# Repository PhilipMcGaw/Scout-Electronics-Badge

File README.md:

====== Electronics badge ======

How to earn your badge:

  - Identify a number of common electronic components that are shown to you.
    - Explain, in simple terms, the functions they perform in electronic circuits.
  - Describe the systems used for marking components with their values
    - Demonstrate by identifying the values of resistors and capacitors by their markings. Explain the importance of the rating of a component.
  - Show that you know the symbols used to represent common components in circuit diagrams.
    - Show how to identify the polarity of a diode and a specific PIN on an integrated circuit.
  - Show that you’re aware of the safe working practices to be followed when handling electronic components, circuit boards and when soldering.
  - Use a multimeter to measure voltage, current and resistance in a simple circuit.
    - Explain the relationship between these values.
  - Talk about the main differences in the operation of digital and analogue circuits.
  - Construct three simple circuits.
    - One of these should be based mainly on digital electronics. They can be from a book or magazine, or you can design the circuits yourself. If possible, at least one of the circuits should be soldered using either stripboard or a custom-made printed circuit board.
  - Explain the principles behind the operation of each circuit and the typical values of voltage and current found in each.
  - Explain the possible uses of the three circuits you built.
  - Talk about the uses and benefits of electronics in everyday life.
    - Explain how electronics can be used to improve lives.

| Number  | Title                                                                                                                     | 1  | 2  | 3  | 4  | 5  | 6  | 7  | 8  | 9  | 10  |
| 1.      | Learn about resistors https://www.scouts.org.uk/activities/learn-about-resistors/                                         |    | 2  |    |    |    |    |    |    |    |     |
| 2.      | Ready https://www.scouts.org.uk/activities/ready-steady-solder/                                                           |    |    |    | 4  |    |    |    |    |    |     |
| 3.      | Multimeter multi-you https://www.scouts.org.uk/activities/multimeter-multi-you/                                           |    |    |    |    | 5  |    |    |    |    |     |
| 4.      | Thinking logically https://www.scouts.org.uk/activities/thinking-logically/                                               |    |    |    |    |    | 6  |    |    |    |     |
| 5.      | Brush bugs https://www.scouts.org.uk/activities/brush-bugs/ / https://kitronik.co.uk/blogs/resources/iet-scout-brush-bug  |    |    |    |    |    |    | 7  | 8  | 9  |     |
| 6.      | Fruit and Vegetable Power Challenge https://www.scouts.org.uk/activities/fruit-and-vegetable-power-challenge/             |    |    |    |    |    |    | 7  |    |    |     |
| 7.      | LEDs Celebrate https://www.scouts.org.uk/activities/leds-celebrate/                                                       |    |    |    |    |    |    | 7  | 8  | 9  |     |
| 8.      | Make an electric car https://www.scouts.org.uk/activities/make-an-electric-car/                                           |    |    |    |    |    |    | 7  |    |    |     |
| 9.      | Making rainbows https://www.scouts.org.uk/activities/making-rainbows/                                                     |    |    |    |    |    |    | 7  | 8  | 9  |     |
| 10.     | Power a lightbulb using potato energy https://www.scouts.org.uk/activities/power-a-lightbulb-using-potato-energy/         |    |    |    |    |    |    |    |    |    | 10  |

  * https://kitronik.co.uk/blogs/resources/scout-electronics-badge-resources
  * https://www.scouting.org/merit-badges/electronics/
  * https://cobargoscouts.org.au/jota-joti-electronics.html

  - Describe the safety precautions you must exercise when using, building, altering, or repairing electronic devices.
  - Do the following:
    - Draw a simple schematic diagram. It must show resistors, capacitors, and transistors or integrated circuits. Use the correct symbols. Label all parts.
    - Tell the purpose of each part.
  - Do the following:
    - Show the right way to solder and desolder.
    - Show how to avoid heat damage to electronic components.
    - Tell about the function of a printed circuit board. Tell what precautions should be observed when soldering printed circuit boards.
  - Do the following:
    - Discuss each of the following with your counselor:
      - How to use electronics for a control purpose.
      - Explain the basic principles of digital logic.
      - How to use electronics for three different analog applications.
    - Show how to change three decimal numbers into binary numbers and three binary numbers into decimal numbers.
    - Choose ONE of the following THREE projects. For your project, find or create a schematic diagram. To the best of your ability, explain to your counselor how the circuit you built operates.
      - A control device
      - A digital circuit
      - An analog circuit.
  - Do the following:
    - Show how to solve a simple problem involving current, voltage, and resistance using Ohm's law
    - Tell about the need for and the use of test equipment in electronics. Name three types of test equipment. Tell how they operate.
    - Demonstrate to your counsellor how to read the colored bands of a resistor to determine its resistance value.
    - Explain the differences between Through Hole and Surface Mount assembly technologies and give three advantages of each.
  - Identify three career opportunities that would use skills and knowledge in Electronics. Pick one and research the training, education, certification requirements, experience, and expenses associated with entering the field. Research the prospects for employment, starting salary, advancement opportunities and career goals associated with this career. Discuss what you learned with your counselor and whether you might be interested in this career.

  https://docs.franzininho.com.br/docs/franzininho-diy/sobre#projeto-open-hardware

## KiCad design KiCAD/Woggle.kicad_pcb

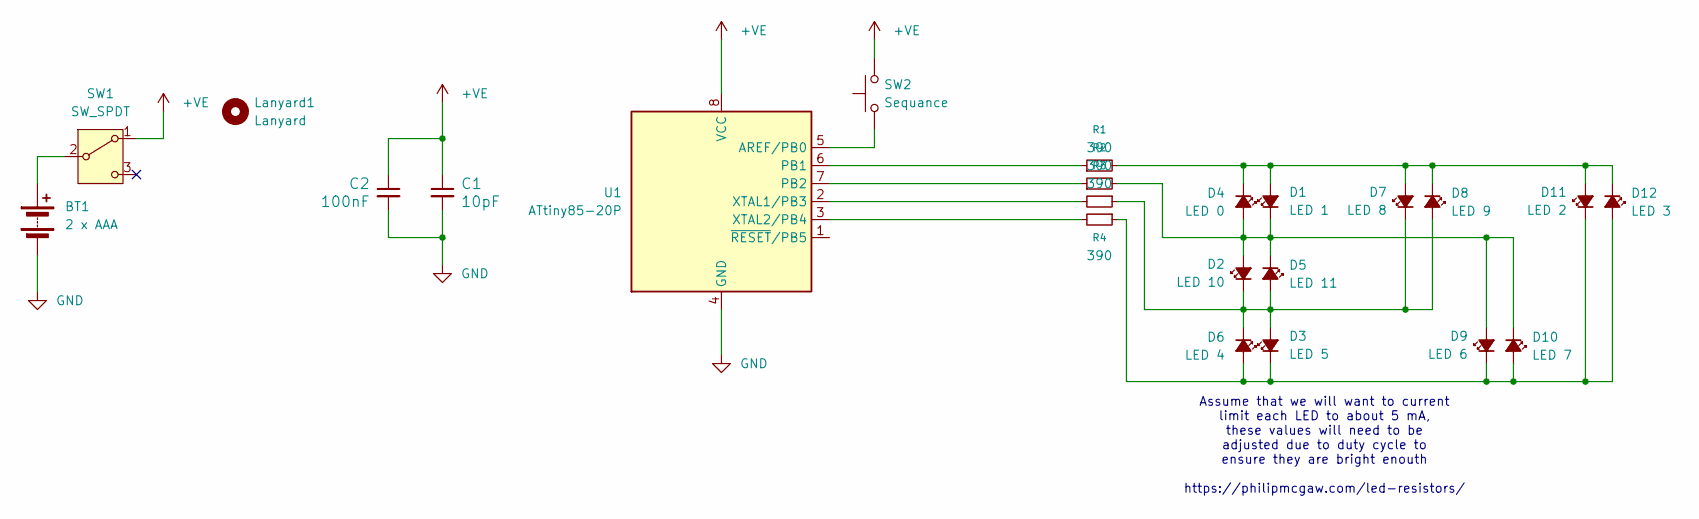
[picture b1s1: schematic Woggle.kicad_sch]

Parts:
BT1: 2 x AAA; Scouts - 2 x AAA battery cell holder
C1: 10pF; C_Disc_D4.7mm_W2.5mm_P5.00mm
C2: 100nF; C_Disc_D4.7mm_W2.5mm_P5.00mm
D1: LED 1; Scouts - 5mm LED
D2: LED 10; Scouts - 5mm LED
D3: LED 5; Scouts - 5mm LED
D4: LED 0; Scouts - 5mm LED
D5: LED 11; Scouts - 5mm LED
D6: LED 4; Scouts - 5mm LED
D7: LED 8; Scouts - 5mm LED
D8: LED 9; Scouts - 5mm LED
D9: LED 6; Scouts - 5mm LED
D10: LED 7; Scouts - 5mm LED
D11: LED 2; Scouts - 5mm LED
D12: LED 3; Scouts - 5mm LED
Lanyard1: Lanyard; MountingHole_5mm
R1, R2, R3, R4: 390; Scouts - Resistor (10.16mm)
SW1: SW_SPDT; SW_Slide_SPDT_Angled_CK_OS102011MA1Q
SW2: Sequance; SW_PUSH-12mm
U1: ATtiny85-20P; Scouts - DIP 8

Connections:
+VE: C1.1, C2.1, SW1.1 (A), SW2.2, U1.8 (VCC)
GND: BT1.2 (-), C1.2, C2.2, U1.4 (GND)
unnamed: BT1.1 (+), SW1.2 (B)
unnamed: D1.2 (A), D4.1 (K), D7.2 (A), D8.1 (K), D11.2 (A), D12.1 (K), R1.2
unnamed: D1.1 (K), D2.2 (A), D4.2 (A), D5.1 (K), D9.2 (A), D10.1 (K), R2.2
unnamed: D2.1 (K), D3.2 (A), D5.2 (A), D6.1 (K), D7.1 (K), D8.2 (A), R3.1
unnamed: D3.1 (K), D6.2 (A), D9.1 (K), D10.2 (A), D11.1 (K), D12.2 (A), R4.1
unnamed: SW2.1, U1.5 (AREF/PB0)
unnamed: R1.1, U1.6 (PB1)
unnamed: R2.1, U1.7 (PB2)
unnamed: R3.2, U1.2 (XTAL1/PB3)
unnamed: R4.2, U1.3 (XTAL2/PB4)

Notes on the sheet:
Assume that we will want to current limit each LED to about 5 mA, these values will need to be adjusted due to duty cycle to ensure they are bright enouth https://philipmcgaw.com/led-resistors/

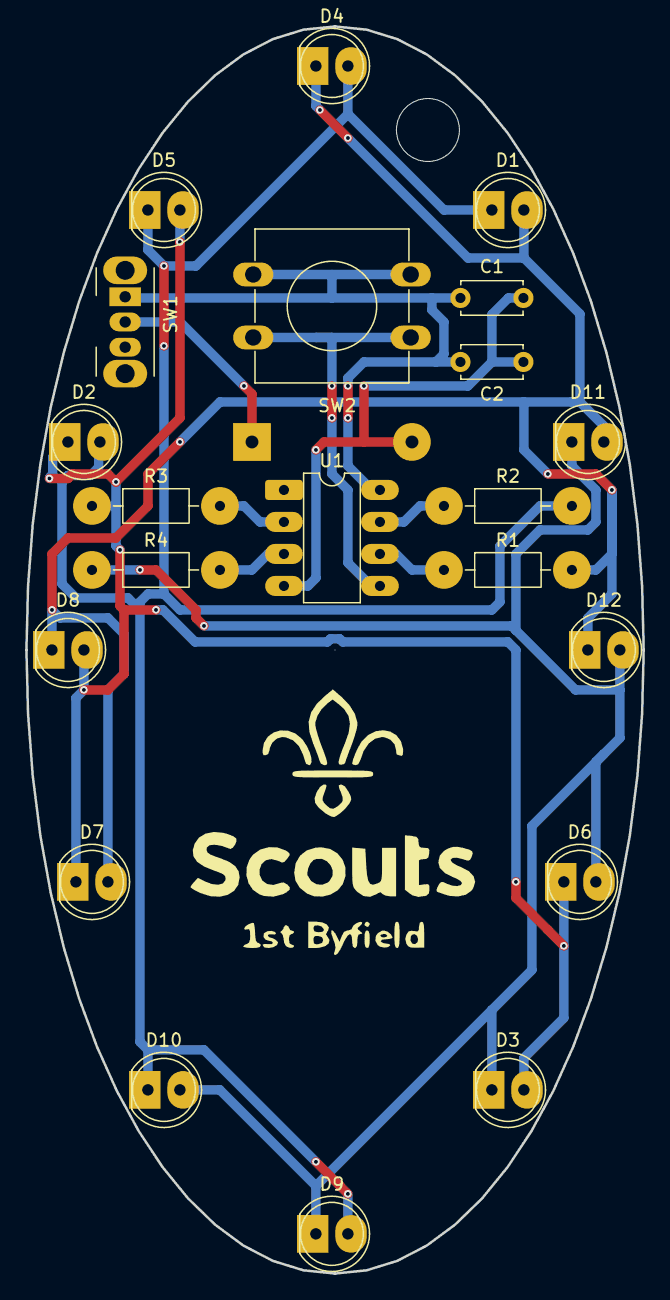
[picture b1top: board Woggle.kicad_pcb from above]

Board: 2 copper layers, 49.0 x 99.0 mm, 23 parts (1 on the bottom side), 12 nets.

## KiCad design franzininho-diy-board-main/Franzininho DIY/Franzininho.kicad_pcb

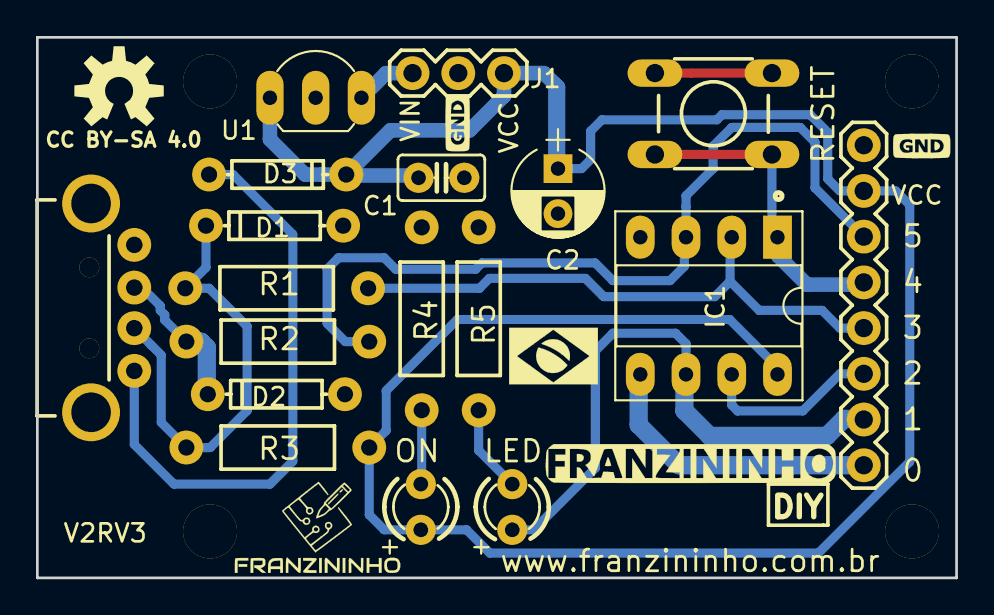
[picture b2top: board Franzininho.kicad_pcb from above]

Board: 2 copper layers, 51.1 x 30.0 mm, 23 parts (0 on the bottom side), 14 nets.

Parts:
@HOLE0, @HOLE1, @HOLE2, @HOLE3: (no value)
C1: 0.1uf; C025-025X050
C2: 10uF; CP_Radial_D5.0mm_P2.50mm
D1, D2: BZT52; DIODE-BZT52
D3: 1N4148; DIODE-1N4148
IC1: ATTINY85 - 20PU; DIP-8_W7.62mm_Socket_LongPads
J1: M03PTH; 1X03
JP3: M08; 1X08_ROUND
LED: LED3MM
LOGO1: OSHW-LOGOM; OSHW-LOGO-M
ON: LED3MM
R1, R2: 68R; AXIAL-0.4
R3: 1K5; AXIAL-0.4
R4, R5: 1K; AXIAL-0.4
RESET: TACTILE-SWITCH-PTH; TAC-SWITCH-PTH
U1: L78L05_TO92; TO-92_Inline_Wide
X1: USB-A-H

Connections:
5V: C1.1, C2.1, D3.C, IC1.8, J1.1, JP3.7, ON.A, R3.P$1, U1.1
GND: C1.2, C2.2, D1.A, D2.A, IC1.4, J1.2, JP3.8, R4.P$1, R5.P$1, RESET.3, RESET.4, U1.2, X1.GND
unnamed: D1.C, R1.P$1, R3.P$2, X1.D-
unnamed: D2.C, R2.P$1, X1.D+
unnamed: D3.A, X1.VBUS
unnamed: IC1.1, JP3.5, RESET.1, RESET.2
unnamed: IC1.2, JP3.4, R1.P$2
unnamed: IC1.3, JP3.6, R2.P$2
unnamed: IC1.5, JP3.1
unnamed: IC1.6, JP3.2, LED.A
unnamed: IC1.7, JP3.3
unnamed: J1.3, U1.3
unnamed: LED.K, R5.P$2
unnamed: ON.K, R4.P$2

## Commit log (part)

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2026-06-11 edited git ignore and git attributes

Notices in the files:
franzininho-diy-board-main/Franzininho DIY/Franzininho.kicad_pcb:
CC BY-SA 4.0
